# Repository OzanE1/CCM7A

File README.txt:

Starting assembly for CCMY 09.05.2025

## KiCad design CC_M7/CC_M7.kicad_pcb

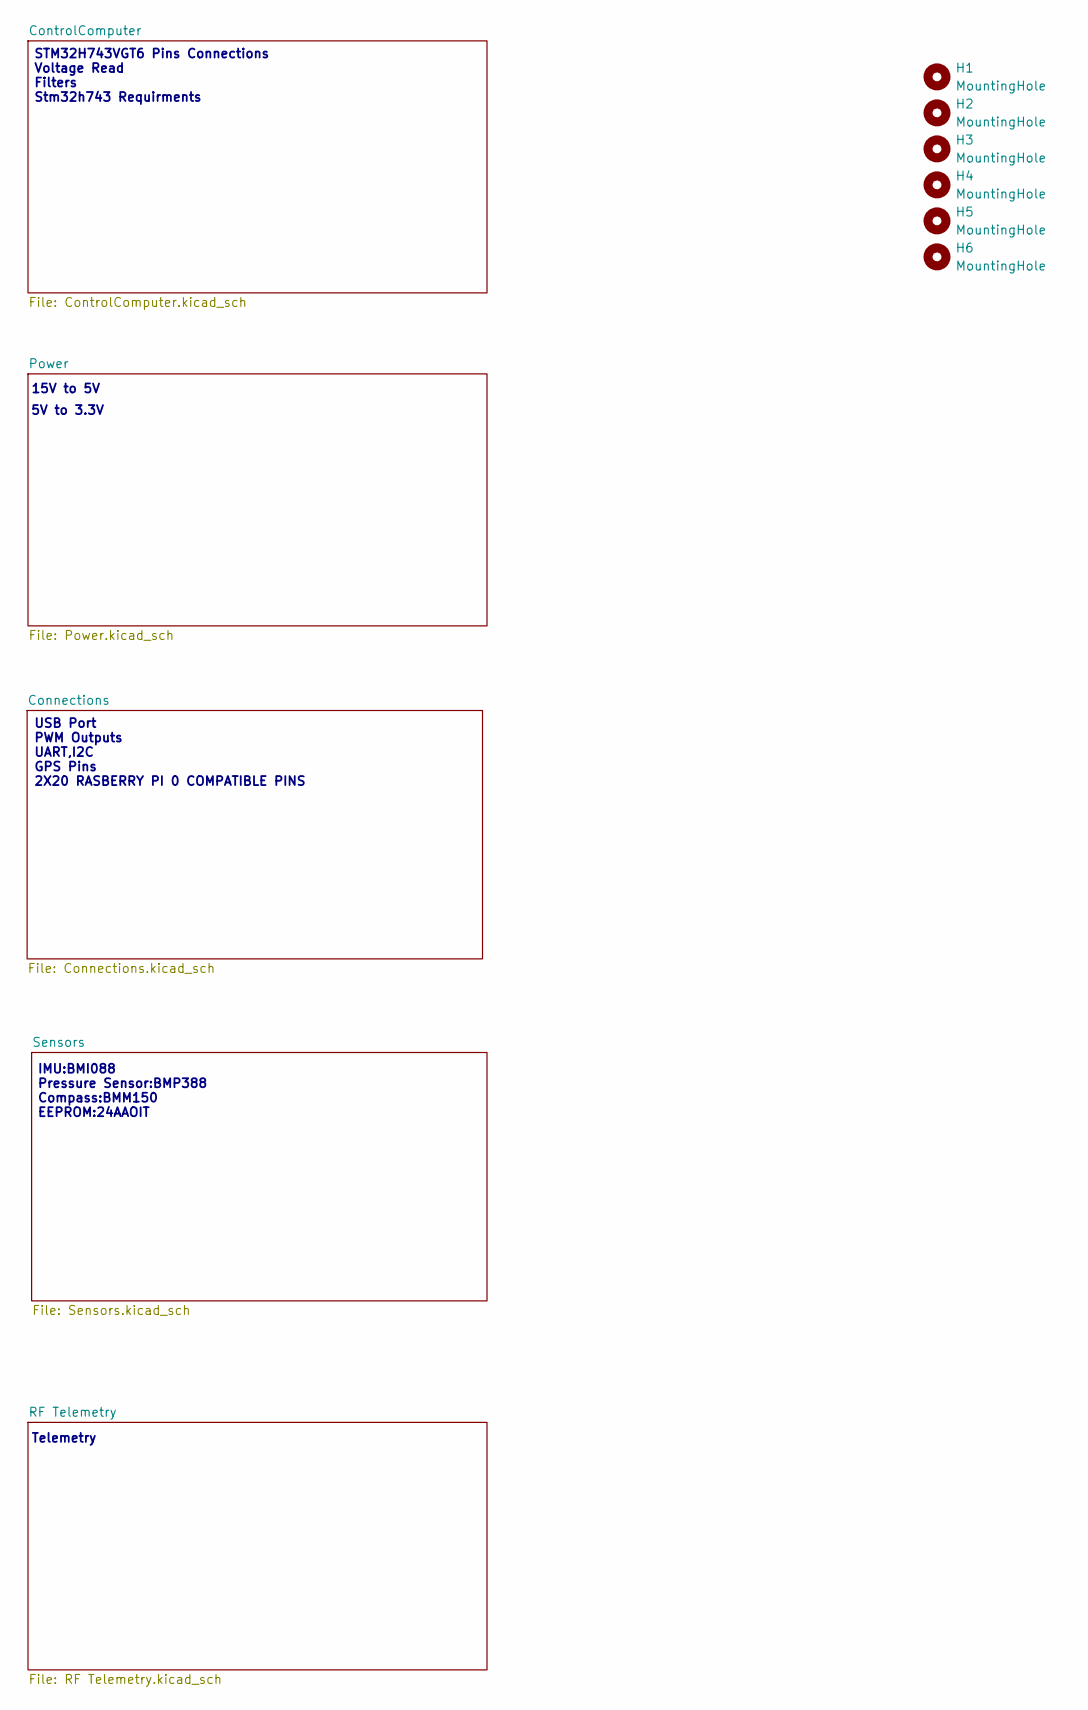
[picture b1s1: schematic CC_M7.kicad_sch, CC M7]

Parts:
H1, H2, H3, H4, H5, H6: MountingHole; CCMountingHole

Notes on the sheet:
15V to 5V
5V to 3.3V
USB Port PWM Outputs UART,I2C GPS Pins 2X20 RASBERRY PI 0 COMPATIBLE PINS
Telemetry
STM32H743VGT6 Pins Connections Voltage Read Filters Stm32h743 Requirments
IMU:BMI088 Pressure Sensor:BMP388 Compass:BMM150 EEPROM:24AAOIT

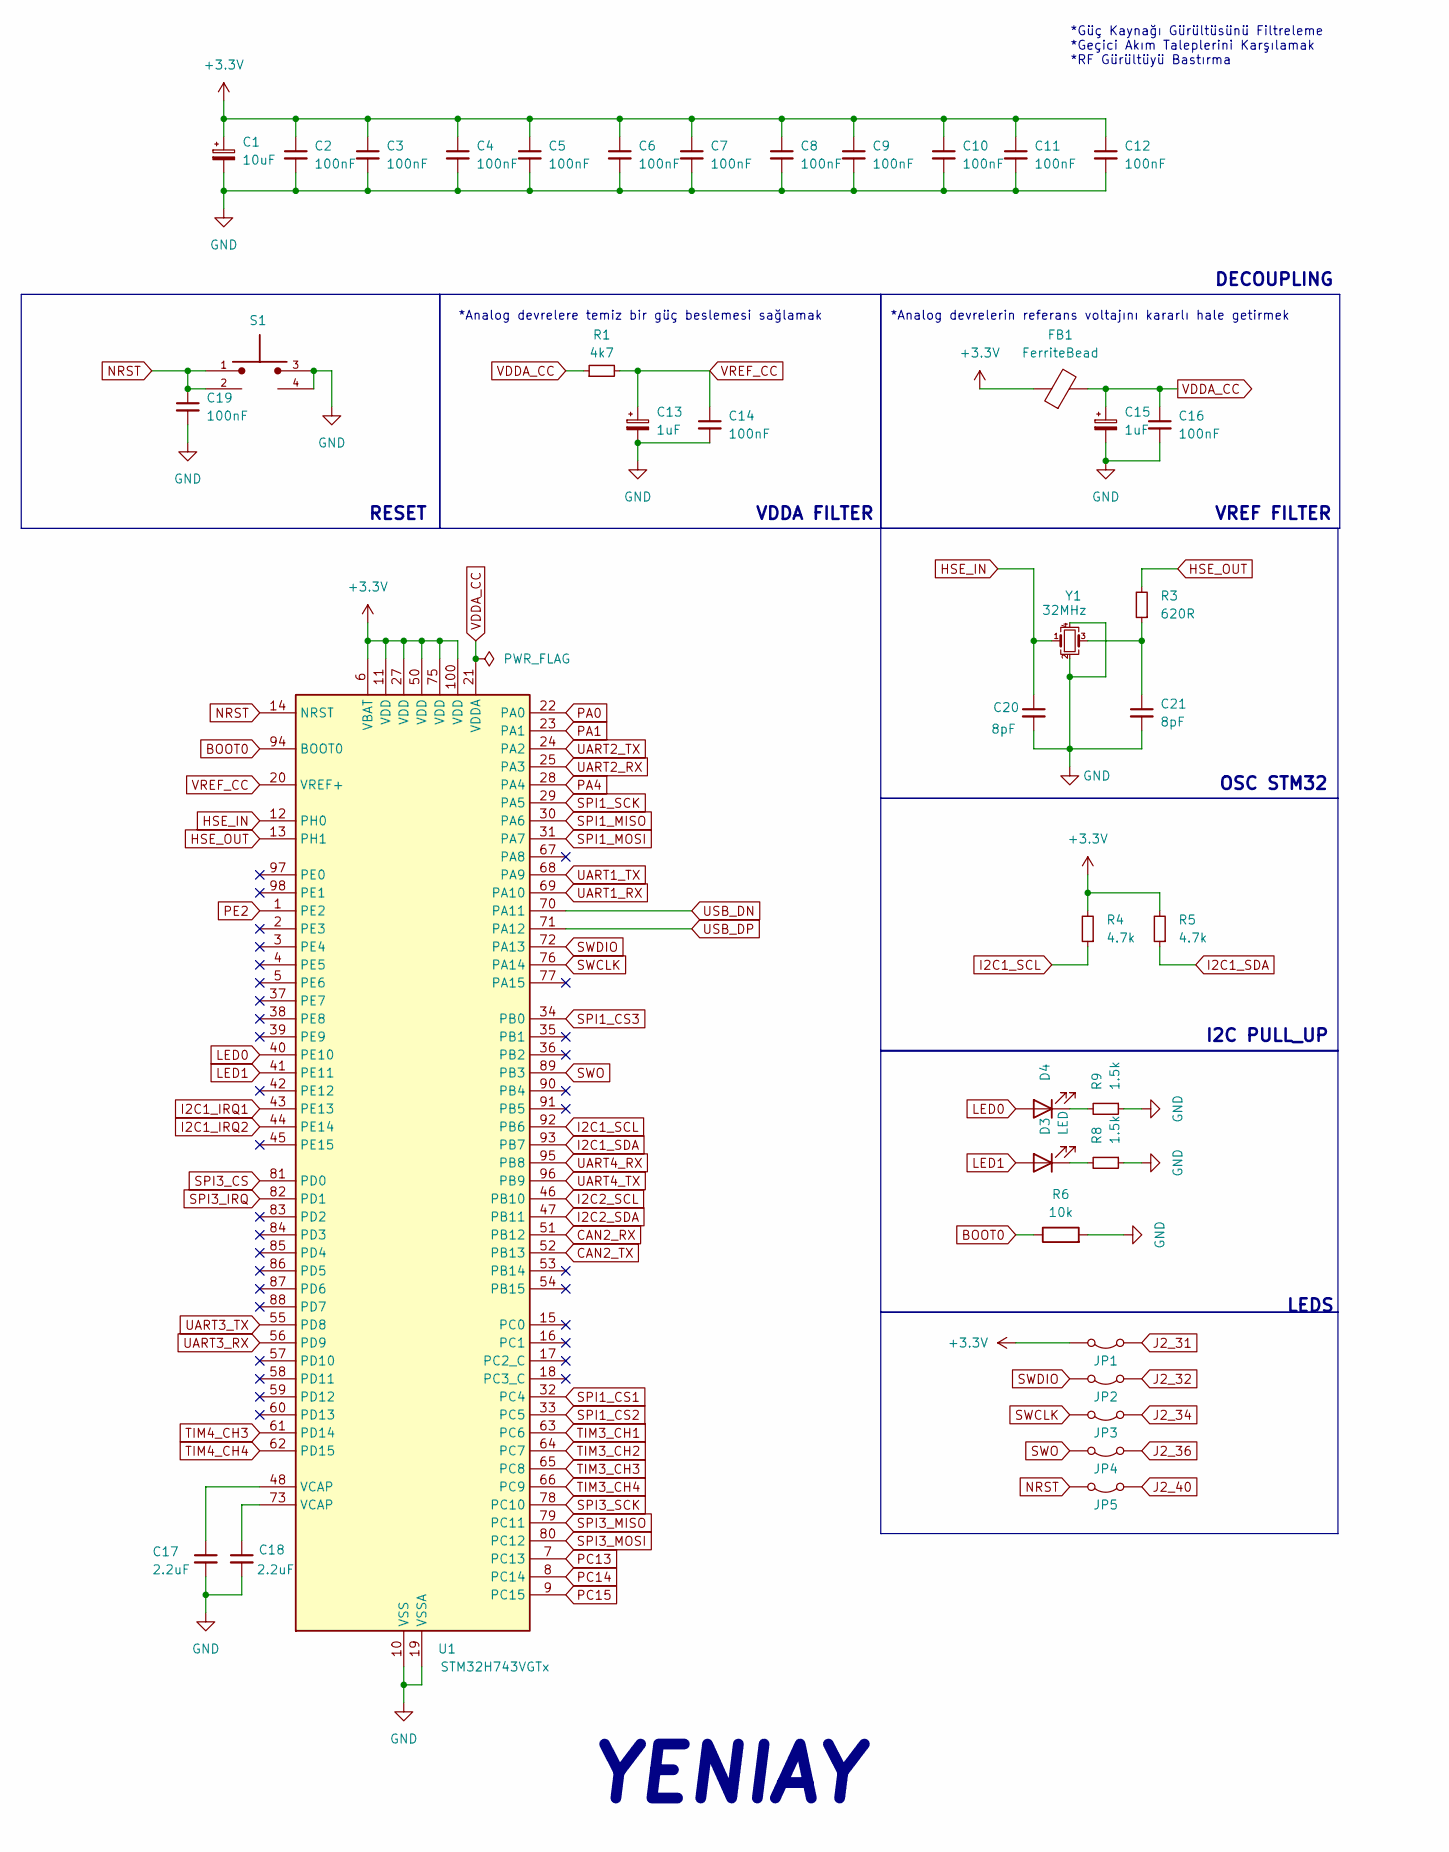
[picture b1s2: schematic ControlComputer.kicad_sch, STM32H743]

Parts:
C1: 10uF; C_0402_1005Metric
C2, C3, C4, C5, C6, C7, C8, C9, C10, C11, C12, C14, C16, C19: 100nF; C_0402_1005Metric
C13, C15: 1uF; C_0402_1005Metric
C17, C18: 2.2uF; C_0402_1005Metric
C20, C21: 8pF; C_0402_1005Metric
D3, D4: LED; LED_0603_1608Metric
FB1: FerriteBead; L_0603_1608Metric
JP1, JP2, JP3, JP4, JP5: SWDIO; SolderJumper-2_P1.3mm_Open_TrianglePad1.0x1.5mm
R1: 4k7; R_0402_1005Metric
R3: 620R; R_0402_1005Metric
R4, R5: 4.7k; R_0402_1005Metric
R6: 10k; R_0402_1005Metric
R8, R9: 1.5k; R_0402_1005Metric
S1: SKRPABE010; SW_SKRPABE010
U1: STM32H743VGTx; LQFP-100_14x14mm_P0.5mm
Y1: 32MHz; Crystal_SMD_3225-4Pin_3.2x2.5mm

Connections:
+3.3V: C1.1, C2.1, C3.1, C4.1, C5.1, C6.1, C7.1, C8.1, C9.1, C10.1, C11.1, C12.1, FB1.1, JP1.2 (B), R4.2, R5.2, U1.6 (VBAT), U1.11 (VDD), U1.27 (VDD), U1.50 (VDD), U1.75 (VDD), U1.100 (VDD); also elsewhere on the board
BOOT0: R6.1, U1.94 (BOOT0)
CAN2_RX: U1.51 (PB12); also elsewhere on the board
CAN2_TX: U1.52 (PB13); also elsewhere on the board
GND: C1.2, C2.2, C3.2, C4.2, C5.2, C6.2, C7.2, C8.2, C9.2, C10.2, C11.2, C12.2, C13.2, C14.2, C15.2, C16.2, C17.2, C18.2, C19.2, C20.2, C21.2, R6.2, R8.1, R9.1, S1.3, S1.4, U1.10 (VSS), U1.19 (VSSA), U1.26 (VSS), U1.49 (VSS), U1.74 (VSS), U1.99 (VSS), Y1.2, Y1.4; also elsewhere on the board
HSE_IN: C20.1, U1.12 (PH0), Y1.1
HSE_OUT: R3.2, U1.13 (PH1)
I2C1_IRQ1: U1.43 (PE13); also elsewhere on the board
I2C1_IRQ2: U1.44 (PE14); also elsewhere on the board
I2C1_SCL: R4.1, U1.92 (PB6); also elsewhere on the board
I2C1_SDA: R5.1, U1.93 (PB7); also elsewhere on the board
I2C2_SCL: U1.46 (PB10); also elsewhere on the board
I2C2_SDA: U1.47 (PB11); also elsewhere on the board
J2_31: JP1.1 (A); also elsewhere on the board
J2_32: JP2.1 (A); also elsewhere on the board
J2_34: JP3.1 (A); also elsewhere on the board
J2_36: JP4.1 (A); also elsewhere on the board
J2_40: JP5.1 (A); also elsewhere on the board
LED0: D4.2 (A), U1.40 (PE10)
LED1: D3.2 (A), U1.41 (PE11)
NRST: C19.1, JP5.2 (B), S1.1, S1.2, U1.14 (NRST)
unnamed: C17.1, U1.48 (VCAP)
unnamed: C18.1, U1.73 (VCAP)
unnamed: C21.1, R3.1, Y1.3
unnamed: D3.1 (K), R8.2
unnamed: D4.1 (K), R9.2
PA0: U1.22 (PA0); also elsewhere on the board
PA1: U1.23 (PA1); also elsewhere on the board
PA4: U1.28 (PA4); also elsewhere on the board
PC13: U1.7 (PC13); also elsewhere on the board
PC14: U1.8 (PC14); also elsewhere on the board
PC15: U1.9 (PC15); also elsewhere on the board
PE2: U1.1 (PE2); also elsewhere on the board
SPI1_CS1: U1.32 (PC4); also elsewhere on the board
SPI1_CS2: U1.33 (PC5); also elsewhere on the board
SPI1_CS3: U1.34 (PB0); also elsewhere on the board
SPI1_MISO: U1.30 (PA6); also elsewhere on the board
SPI1_MOSI: U1.31 (PA7); also elsewhere on the board
SPI1_SCK: U1.29 (PA5); also elsewhere on the board
SPI3_CS: U1.81 (PD0); also elsewhere on the board
SPI3_IRQ: U1.82 (PD1); also elsewhere on the board
SPI3_MISO: U1.79 (PC11); also elsewhere on the board
SPI3_MOSI: U1.80 (PC12); also elsewhere on the board
SPI3_SCK: U1.78 (PC10); also elsewhere on the board
SWCLK: JP3.2 (B), U1.76 (PA14)
SWDIO: JP2.2 (B), U1.72 (PA13)
SWO: JP4.2 (B), U1.89 (PB3)
TIM3_CH1: U1.63 (PC6); also elsewhere on the board
TIM3_CH2: U1.64 (PC7); also elsewhere on the board
TIM3_CH3: U1.65 (PC8); also elsewhere on the board
TIM3_CH4: U1.66 (PC9); also elsewhere on the board
TIM4_CH3: U1.61 (PD14); also elsewhere on the board
TIM4_CH4: U1.62 (PD15); also elsewhere on the board
UART1_RX: U1.69 (PA10); also elsewhere on the board
UART1_TX: U1.68 (PA9); also elsewhere on the board
UART2_RX: U1.25 (PA3); also elsewhere on the board
UART2_TX: U1.24 (PA2); also elsewhere on the board
UART3_RX: U1.56 (PD9); also elsewhere on the board
UART3_TX: U1.55 (PD8); also elsewhere on the board
UART4_RX: U1.95 (PB8); also elsewhere on the board
UART4_TX: U1.96 (PB9); also elsewhere on the board
USB_DN: U1.70 (PA11); also elsewhere on the board
USB_DP: U1.71 (PA12); also elsewhere on the board
VDDA_CC: C15.1, C16.1, FB1.2, R1.1, U1.21 (VDDA)
VREF_CC: C13.1, C14.1, R1.2, U1.20 (VREF+)

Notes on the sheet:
*Güç Kaynağı Gürültüsünü Filtreleme *Geçici Akım Taleplerini Karşılamak *RF Gürültüyü Bastırma
*Analog devrelere temiz bir güç beslemesi sağlamak
DECOUPLING
OSC STM32
VREF FILTER
RESET
I2C PULL_UP
*Analog devrelerin referans voltajını kararlı hale getirmek
LEDS
YENIAY
VDDA FILTER

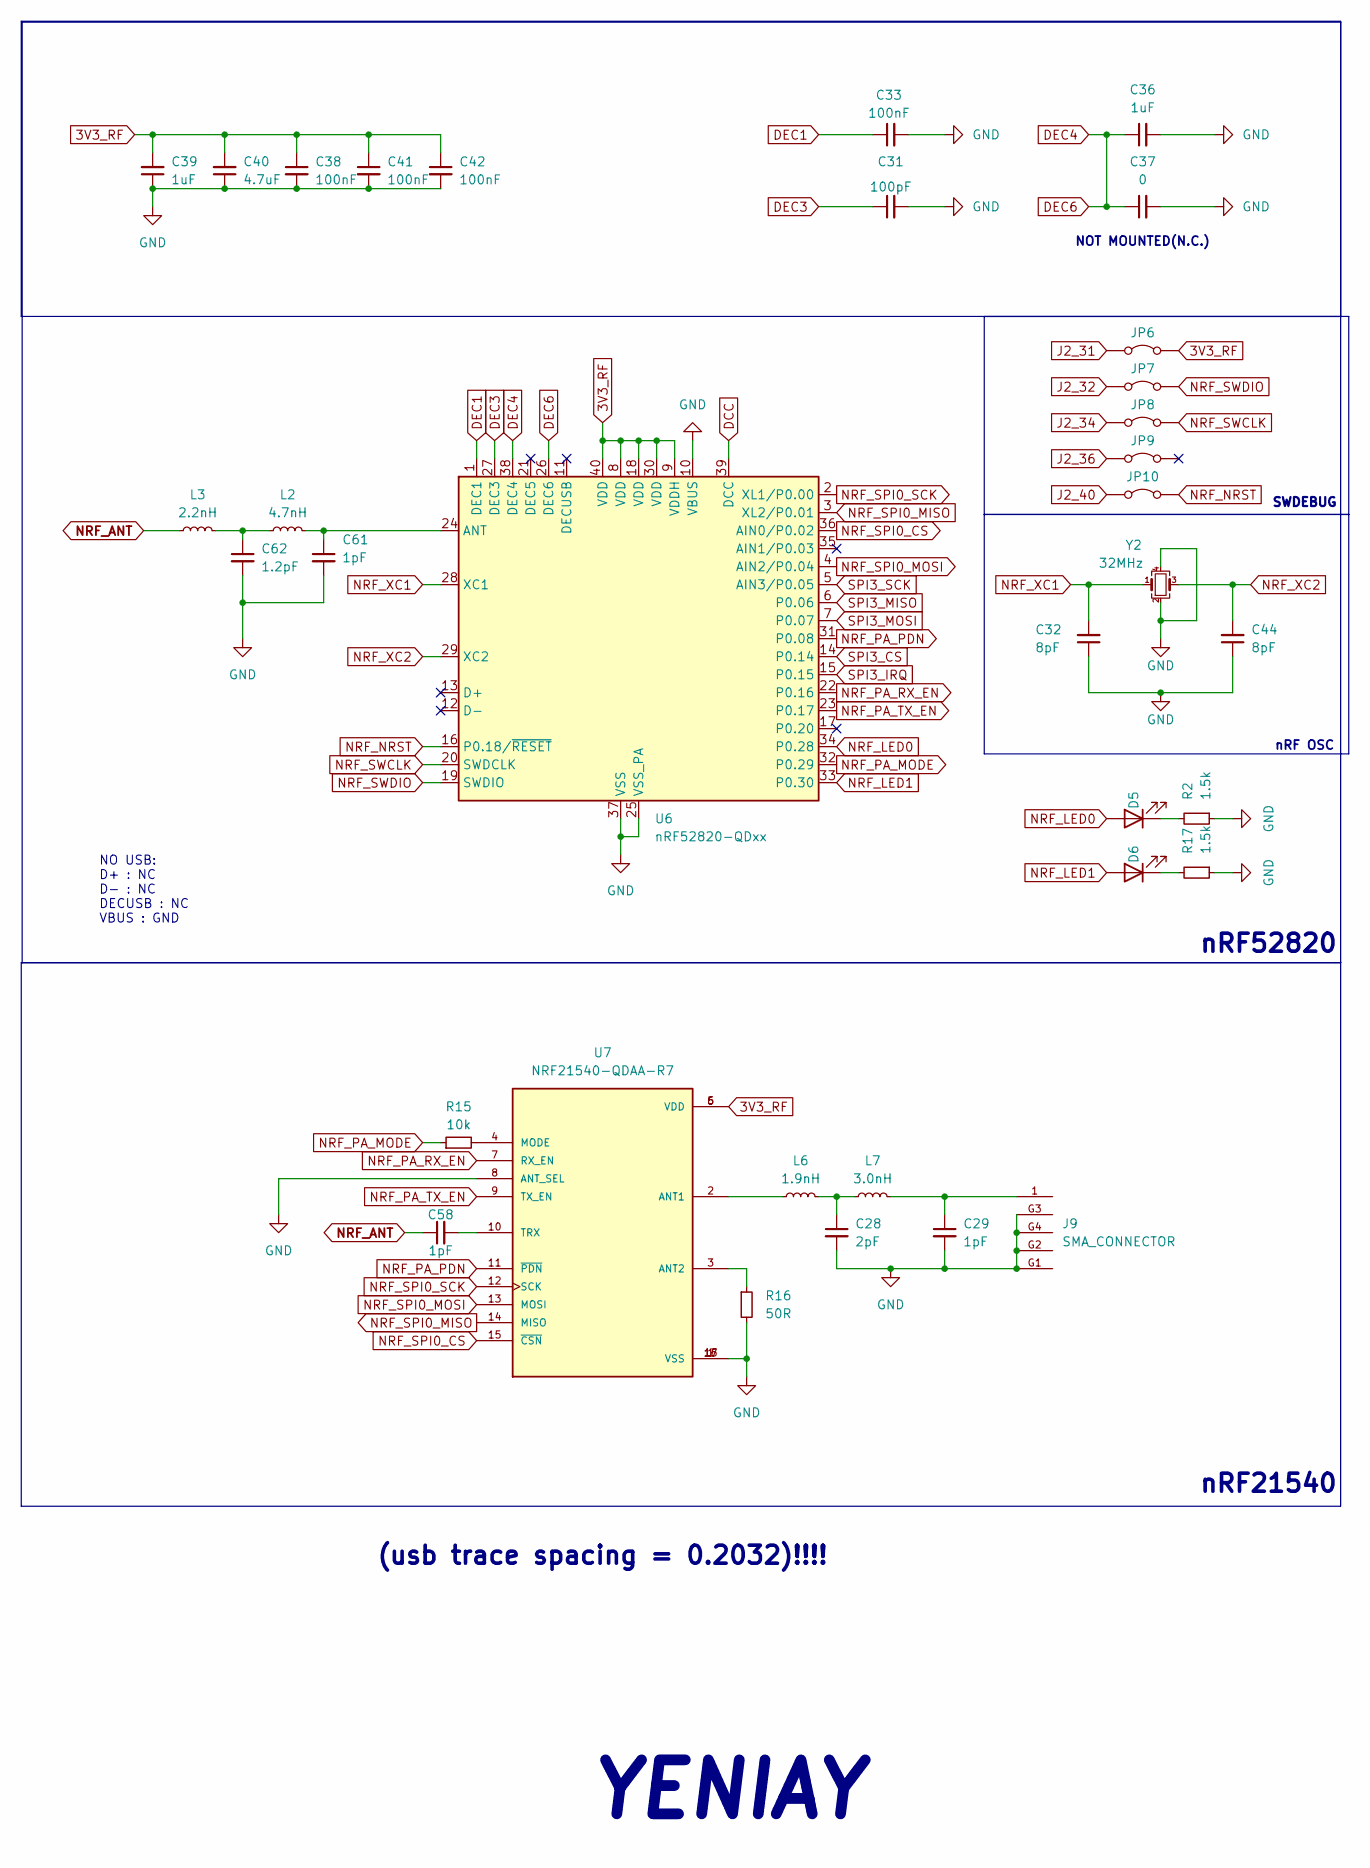
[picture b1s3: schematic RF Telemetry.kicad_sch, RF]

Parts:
C28: 2pF; C_0201_0603Metric
C29, C58, C61: 1pF; C_0201_0603Metric
C31: 100pF; C_0402_1005Metric
C32, C44: 8pF; C_0402_1005Metric
C33, C38, C41, C42: 100nF; C_0402_1005Metric
C36, C39: 1uF; C_0402_1005Metric
C37: 0; C_0402_1005Metric
C40: 4.7uF; C_0603_1608Metric
C62: 1.2pF; C_0201_0603Metric
D5, D6: LED; LED_0805_2012Metric
J9: SMA_CONNECTOR; LPRS_SMA_CONNECTOR; PARTREV 1.3
JP6, JP7, JP8, JP9, JP10: SWDIO; SolderJumper-2_P1.3mm_Open_TrianglePad1.0x1.5mm
L2: 4.7nH; L_0201_0603Metric
L3: 2.2nH; L_0201_0603Metric
L6: 1.9nH; L_0201_0603Metric
L7: 3.0nH; L_0201_0603Metric
R2, R17: 1.5k; R_0402_1005Metric
R15: 10k; R_0402_1005Metric
R16: 50R; R_0402_1005Metric
U6: nRF52820-QDxx; QFN-40-1EP_5x5mm_P0.4mm_EP3.6x3.6mm
U7: NRF21540-QDAA-R7; QFN65P400X400X95-17N; PARTREV 1.0
Y2: 32MHz; Crystal_SMD_3225-4Pin_3.2x2.5mm

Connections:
3V3_RF: C38.1, C39.2, C40.2, C41.1, C42.1, JP6.2 (B), U6.8 (VDD), U6.9 (VDDH), U6.18 (VDD), U6.30 (VDD), U6.40 (VDD), U7.5 (VDD), U7.6 (VDD); also elsewhere on the board
DCC: U6.39 (DCC)
DEC1: C33.1, U6.1 (DEC1)
DEC3: C31.1, U6.27 (DEC3)
DEC4: C36.1, C37.1, U6.26 (DEC6), U6.38 (DEC4)
GND: C28.2, C29.2, C31.2, C32.1, C33.2, C36.2, C37.2, C38.2, C39.1, C40.1, C41.2, C42.2, C44.1, C61.2, C62.2, J9.G1, J9.G2, J9.G3, J9.G4, R2.1, R16.2, R17.1, U6.10 (VBUS), U6.25 (VSS_PA), U6.37 (VSS), U6.41 (VSS), U7.1 (VSS), U7.8 (ANT_SEL), U7.16 (VSS), U7.17 (VSS), Y2.2, Y2.4; also elsewhere on the board
J2_31: JP6.1 (A); also elsewhere on the board
J2_32: JP7.1 (A); also elsewhere on the board
J2_34: JP8.1 (A); also elsewhere on the board
J2_36: JP9.1 (A); also elsewhere on the board
J2_40: JP10.1 (A); also elsewhere on the board
NRF_ANT: C58.1, L3.1
NRF_LED0: D5.2 (A), U6.34 (P0.28)
NRF_LED1: D6.2 (A), U6.33 (P0.30)
NRF_NRST: JP10.2 (B), U6.16 (P0.18/~RESET)
NRF_PA_MODE: R15.1, U6.32 (P0.29)
NRF_PA_PDN: U6.31 (P0.08), U7.11 (~PDN)
NRF_PA_RX_EN: U6.22 (P0.16), U7.7 (RX_EN)
NRF_PA_TX_EN: U6.23 (P0.17), U7.9 (TX_EN)
NRF_SPI0_CS: U6.36 (AIN0/P0.02), U7.15 (~CSN)
NRF_SPI0_MISO: U6.3 (XL2/P0.01), U7.14 (MISO)
NRF_SPI0_MOSI: U6.4 (AIN2/P0.04), U7.13 (MOSI)
NRF_SPI0_SCK: U6.2 (XL1/P0.00), U7.12 (SCK)
NRF_SWCLK: JP8.2 (B), U6.20 (SWDCLK)
NRF_SWDIO: JP7.2 (B), U6.19 (SWDIO)
NRF_XC1: C32.2, U6.28 (XC1), Y2.1
NRF_XC2: C44.2, U6.29 (XC2), Y2.3
unnamed: C28.1, L6.2, L7.1
unnamed: C29.1, J9.1, L7.2
unnamed: C62.1, L2.1, L3.2
unnamed: D5.1 (K), R2.2
unnamed: D6.1 (K), R17.2
unnamed: C61.1, L2.2, U6.24 (ANT)
unnamed: L6.1, U7.2 (ANT1)
unnamed: R16.1, U7.3 (ANT2)
unnamed: R15.2, U7.4 (MODE)
unnamed: C58.2, U7.10 (TRX)
SPI3_CS: U6.14 (P0.14); also elsewhere on the board
SPI3_IRQ: U6.15 (P0.15); also elsewhere on the board
SPI3_MISO: U6.6 (P0.06); also elsewhere on the board
SPI3_MOSI: U6.7 (P0.07); also elsewhere on the board
SPI3_SCK: U6.5 (AIN3/P0.05); also elsewhere on the board

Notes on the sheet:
NO USB: D+ : NC D- : NC DECUSB : NC VBUS : GND
(usb trace spacing = 0.2032)!!!!
nRF21540
nRF52820
YENIAY
NOT MOUNTED(N.C.)
nRF OSC
SWDEBUG

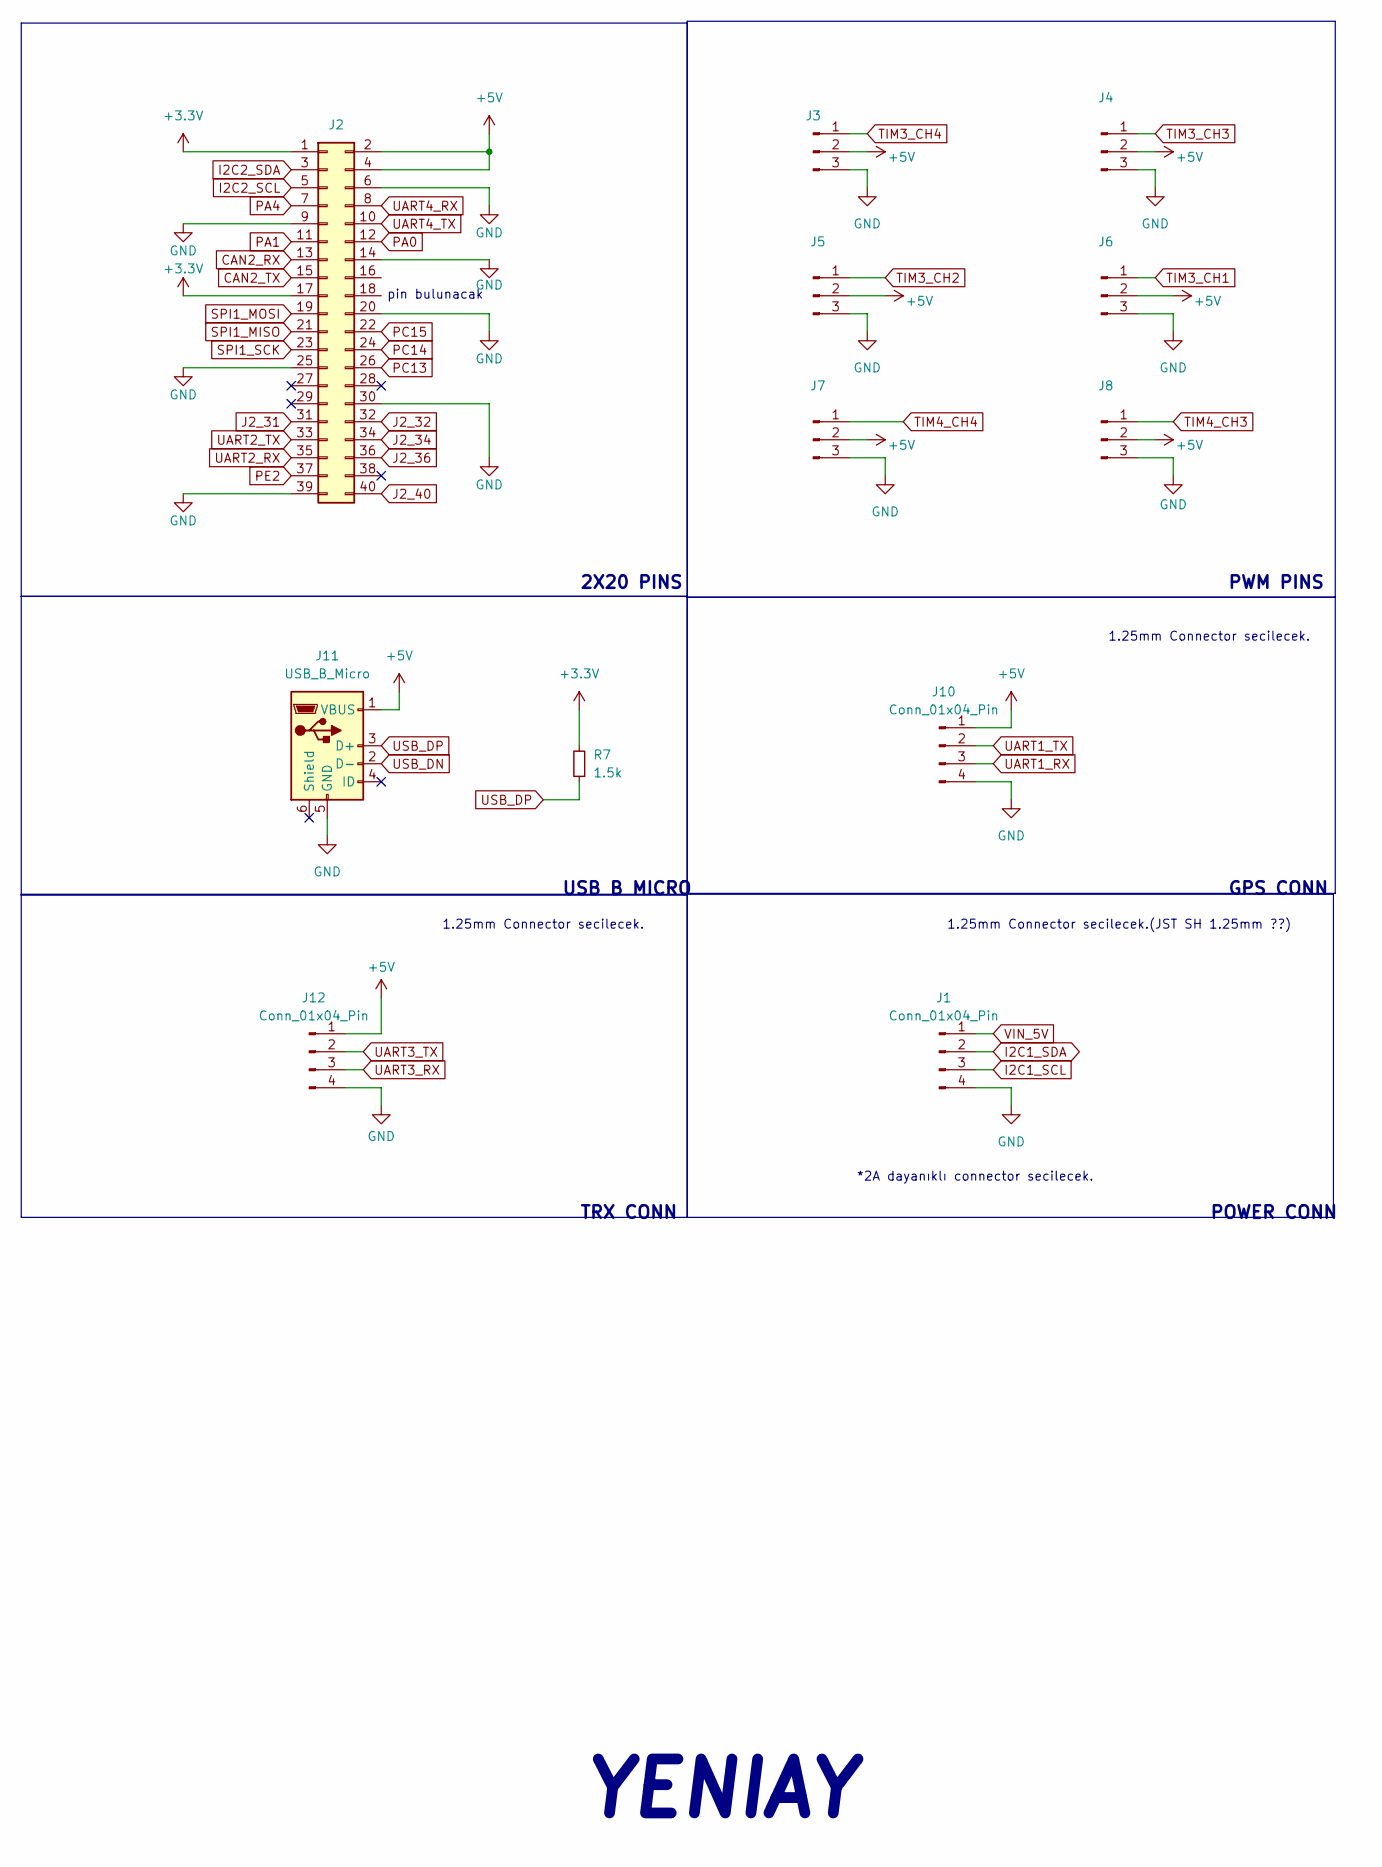
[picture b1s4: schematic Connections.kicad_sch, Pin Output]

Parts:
J1, J10, J12: Conn_01x04_Pin; Hirose_DF13-04P-1.25DSA_1x04_P1.25mm_Vertical
J2: IDC-Header_2x20_P2.54mm_Vertical
J3, J4, J5, J6, J7, J8: Conn_01x03_Pin; 1x03_2.54vertical
J11: USB_B_Micro; USB_Micro-B_Wuerth_629105150521
R7: 1.5k; R_0402_1005Metric

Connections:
+3.3V: J2.1, J2.17, R7.2; also elsewhere on the board
+5V: J2.2, J2.4, J3.2, J4.2, J5.2, J6.2, J7.2, J8.2, J10.1, J11.1 (VBUS), J12.1; also elsewhere on the board
CAN2_RX: J2.13; also elsewhere on the board
CAN2_TX: J2.15; also elsewhere on the board
GND: J1.4, J2.6, J2.9, J2.14, J2.20, J2.25, J2.30, J2.39, J3.3, J4.3, J5.3, J6.3, J7.3, J8.3, J10.4, J11.5 (GND), J12.4; also elsewhere on the board
I2C1_SCL: J1.3; also elsewhere on the board
I2C1_SDA: J1.2; also elsewhere on the board
I2C2_SCL: J2.5; also elsewhere on the board
I2C2_SDA: J2.3; also elsewhere on the board
J2_31: J2.31; also elsewhere on the board
J2_32: J2.32; also elsewhere on the board
J2_34: J2.34; also elsewhere on the board
J2_36: J2.36; also elsewhere on the board
J2_40: J2.40; also elsewhere on the board
PA0: J2.12; also elsewhere on the board
PA1: J2.11; also elsewhere on the board
PA4: J2.7; also elsewhere on the board
PC13: J2.26; also elsewhere on the board
PC14: J2.24; also elsewhere on the board
PC15: J2.22; also elsewhere on the board
PE2: J2.37; also elsewhere on the board
SPI1_MISO: J2.21; also elsewhere on the board
SPI1_MOSI: J2.19; also elsewhere on the board
SPI1_SCK: J2.23; also elsewhere on the board
TIM3_CH1: J6.1; also elsewhere on the board
TIM3_CH2: J5.1; also elsewhere on the board
TIM3_CH3: J4.1; also elsewhere on the board
TIM3_CH4: J3.1; also elsewhere on the board
TIM4_CH3: J8.1; also elsewhere on the board
TIM4_CH4: J7.1; also elsewhere on the board
UART1_RX: J10.3; also elsewhere on the board
UART1_TX: J10.2; also elsewhere on the board
UART2_RX: J2.35; also elsewhere on the board
UART2_TX: J2.33; also elsewhere on the board
UART3_RX: J12.3; also elsewhere on the board
UART3_TX: J12.2; also elsewhere on the board
UART4_RX: J2.8; also elsewhere on the board
UART4_TX: J2.10; also elsewhere on the board
USB_DN: J11.2 (D-); also elsewhere on the board
USB_DP: J11.3 (D+), R7.1; also elsewhere on the board
VIN_5V: J1.1; also elsewhere on the board

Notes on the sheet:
YENIAY
POWER CONN
pin bulunacak
PWM PINS
GPS CONN
1.25mm Connector secilecek.
*2A dayanıklı connector secilecek.
TRX CONN
2X20 PINS
1.25mm Connector secilecek.(JST SH 1.25mm ??)
USB B MICRO

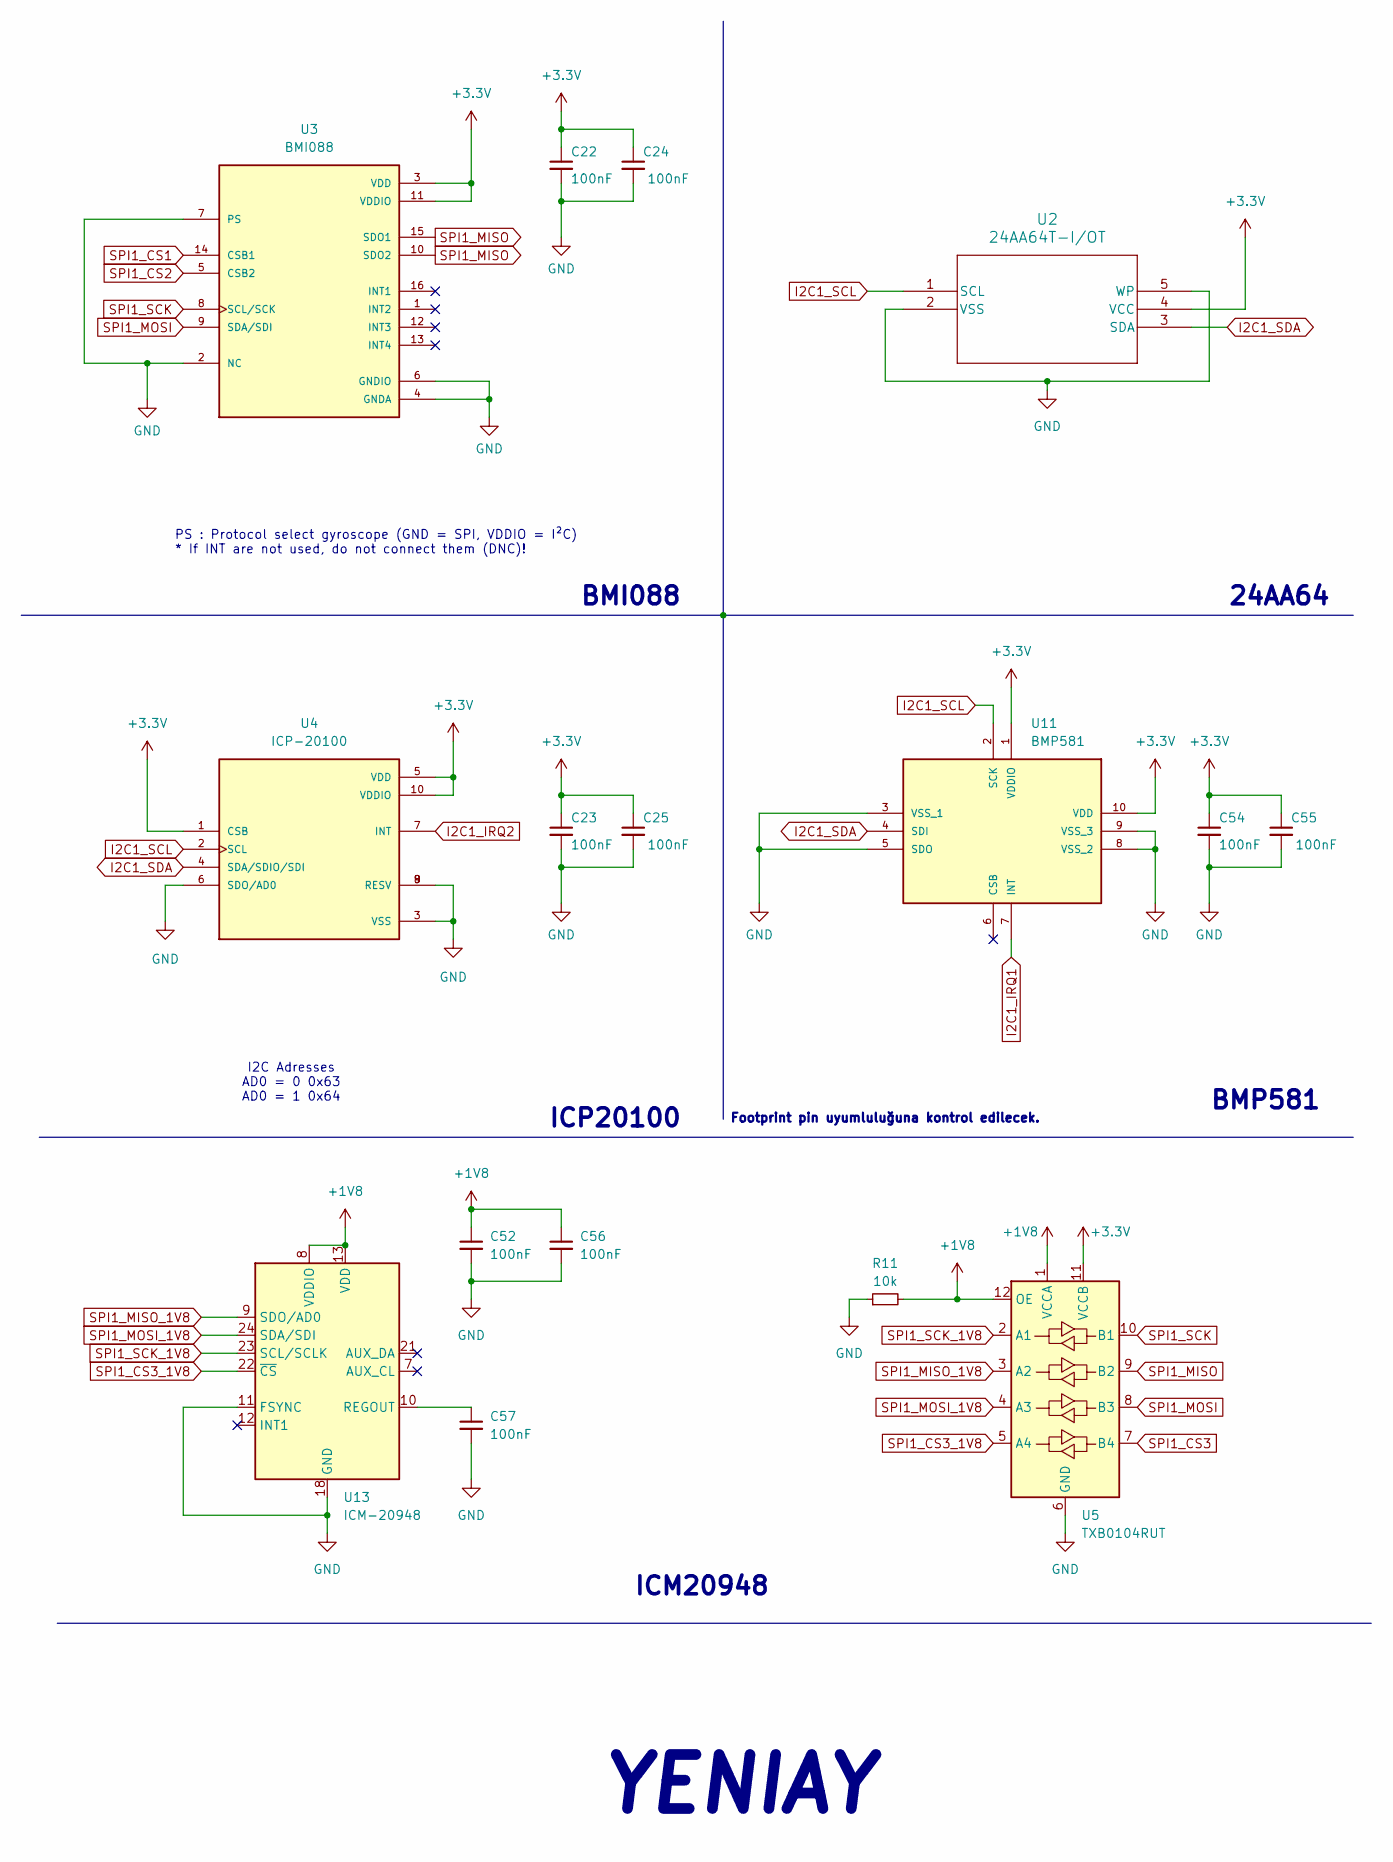
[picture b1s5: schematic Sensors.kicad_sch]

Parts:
C22, C23, C24, C25, C52, C54, C55, C56, C57: 100nF; C_0402_1005Metric
R11: 10k; R_0402_1005Metric
U2: 24AA64T-I/OT; SOT-23-5_HandSoldering
U3: BMI088; PQFN50P450X300X100-16N
U4: ICP-20100; PQFN50P200X200X85-10N; PARTREV 1.1
U5: TXB0104RUT; Texas_R-PUQFN-N12
U11: BMP581; Manufacturer_Part_Number BMP581
U13: ICM-20948; InvenSense_QFN-24_3x3mm_P0.4mm

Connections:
+1V8: C52.1, C56.1, R11.2, U5.1 (VCCA), U5.12 (OE), U13.8 (VDDIO), U13.13 (VDD); also elsewhere on the board
+3.3V: C22.1, C23.1, C24.1, C25.1, C54.1, C55.1, U2.4 (VCC), U3.3 (VDD), U3.11 (VDDIO), U4.1 (CSB), U4.5 (VDD), U4.10 (VDDIO), U5.11 (VCCB), U11.1 (VDDIO), U11.10 (VDD); also elsewhere on the board
GND: C22.2, C23.2, C24.2, C25.2, C52.2, C54.2, C55.2, C56.2, C57.2, R11.1, U2.2 (VSS), U2.5 (WP), U3.2 (NC), U3.4 (GNDA), U3.6 (GNDIO), U3.7 (PS), U4.3 (VSS), U4.6 (SDO/AD0), U4.8 (RESV), U4.9 (RESV), U5.6 (GND), U11.3 (VSS_1), U11.5 (SDO), U11.8 (VSS_2), U11.9 (VSS_3), U13.11 (FSYNC), U13.18 (GND), U13.20 (GND); also elsewhere on the board
I2C1_IRQ1: U11.7 (INT); also elsewhere on the board
I2C1_IRQ2: U4.7 (INT); also elsewhere on the board
I2C1_SCL: U2.1 (SCL), U4.2 (SCL), U11.2 (SCK); also elsewhere on the board
I2C1_SDA: U2.3 (SDA), U4.4 (SDA/SDIO/SDI), U11.4 (SDI); also elsewhere on the board
unnamed: C57.1, U13.10 (REGOUT)
SPI1_CS1: U3.14 (CSB1); also elsewhere on the board
SPI1_CS2: U3.5 (CSB2); also elsewhere on the board
SPI1_CS3: U5.7 (B4); also elsewhere on the board
SPI1_CS3_1V8: U5.5 (A4), U13.22 (~CS)
SPI1_MISO: U3.10 (SDO2), U3.15 (SDO1), U5.9 (B2); also elsewhere on the board
SPI1_MISO_1V8: U5.3 (A2), U13.9 (SDO/AD0)
SPI1_MOSI: U3.9 (SDA/SDI), U5.8 (B3); also elsewhere on the board
SPI1_MOSI_1V8: U5.4 (A3), U13.24 (SDA/SDI)
SPI1_SCK: U3.8 (SCL/SCK), U5.10 (B1); also elsewhere on the board
SPI1_SCK_1V8: U5.2 (A1), U13.23 (SCL/SCLK)

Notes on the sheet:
YENIAY
BMP581
ICM20948
24AA64
Footprint pin uyumluluğuna kontrol edilecek.
ICP20100
I2C Adresses AD0 = 0 0x63 AD0 = 1 0x64
PS : Protocol select gyroscope (GND = SPI, VDDIO = I²C) * If INT are not used, do not connect them (DNC)!
BMI088

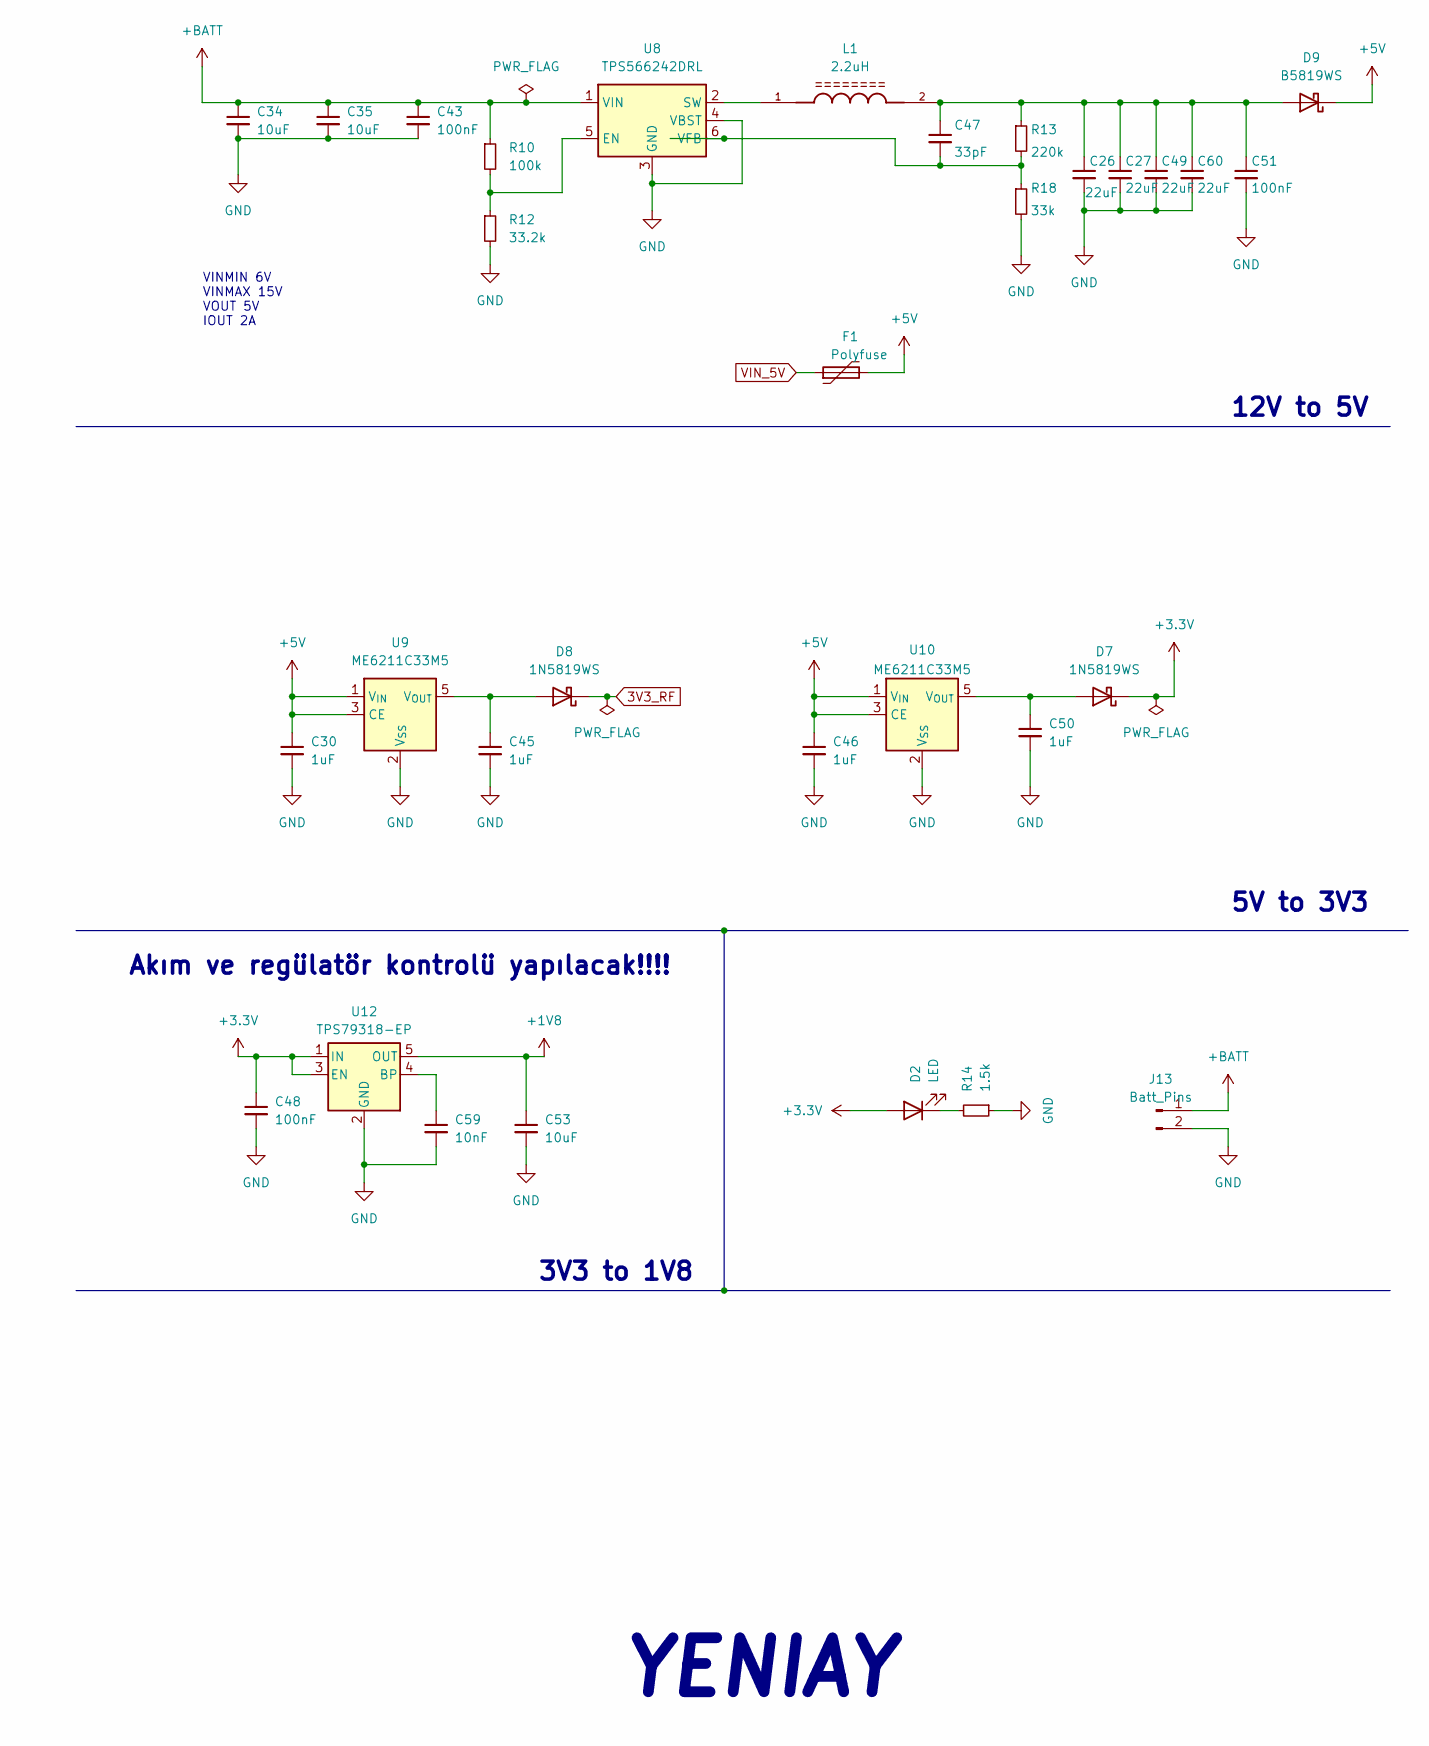
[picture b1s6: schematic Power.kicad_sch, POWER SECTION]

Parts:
C26, C27, C49, C60: 22uF; C_0805_2012Metric
C30, C45, C46, C50: 1uF; C_0805_2012Metric
C34, C35: 10uF; C_0805_2012Metric
C43, C48: 100nF; C_0402_1005Metric
C47: 33pF; C_0402_1005Metric
C51: 100nF; C_0603_1608Metric
C53: 10uF; C_0603_1608Metric
C59: 10nF; C_0402_1005Metric
D2: LED; LED_0603_1608Metric
D7, D8: 1N5819WS; D_SOD-323
D9: B5819WS; D_SOD-323
F1: Polyfuse; Fuse_0805_2012Metric
J13: Batt_Pins; PinSocket_1x02_P2.54mm_Vertical
L1: 2.2uH; IND_SRN6045TA-2R2Y
R10: 100k; R_0603_1608Metric
R12: 33.2k; R_0603_1608Metric
R13: 220k; R_0603_1608Metric
R14: 1.5k; R_0402_1005Metric
R18: 33k; R_0603_1608Metric
U8: TPS566242DRL; SOT-563
U9, U10: ME6211C33M5; SOT-23-5
U12: TPS79318-EP; SOT-23-5

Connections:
3V3_RF: D8.1 (K); also elsewhere on the board
+1V8: C53.1, U12.5 (OUT); also elsewhere on the board
+3.3V: C48.1, D2.2 (A), D7.1 (K), U12.1 (IN), U12.3 (EN); also elsewhere on the board
+5V: C30.1, C46.1, D9.1 (K), F1.2, U9.1 (V_{IN}), U9.3 (CE), U10.1 (V_{IN}), U10.3 (CE); also elsewhere on the board
+BATT: C34.1, C35.1, C43.1, J13.1, R10.1, U8.1 (VIN)
GND: C26.2, C27.2, C30.2, C34.2, C35.2, C43.2, C45.2, C46.2, C48.2, C49.2, C50.2, C51.2, C53.2, C59.2, C60.2, J13.2, R12.2, R14.1, R18.2, U8.3 (GND), U8.4 (VBST), U9.2 (V_{SS}), U10.2 (V_{SS}), U12.2 (GND); also elsewhere on the board
unnamed: D2.1 (K), R14.2
unnamed: C50.1, D7.2 (A), U10.5 (V_{OUT})
unnamed: C45.1, D8.2 (A), U9.5 (V_{OUT})
unnamed: C26.1, C27.1, C47.1, C49.1, C51.1, C60.1, D9.2 (A), L1.2, R13.1
unnamed: R10.2, R12.1, U8.5 (EN)
unnamed: L1.1, U8.2 (SW)
unnamed: C47.2, R13.2, R18.1, U8.6 (VFB)
unnamed: C59.1, U12.4 (BP)
VIN_5V: F1.1; also elsewhere on the board

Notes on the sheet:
YENIAY
3V3 to 1V8
VINMIN 6V VINMAX 15V VOUT 5V IOUT 2A
12V to 5V
5V to 3V3
Akım ve regülatör kontrolü yapılacak!!!!
